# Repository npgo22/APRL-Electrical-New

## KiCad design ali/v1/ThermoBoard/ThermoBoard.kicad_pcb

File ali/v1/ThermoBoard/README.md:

# APRL Thermocouple Board
This is the "old" thermocouple board which was made
as an upgrade to old ALI.

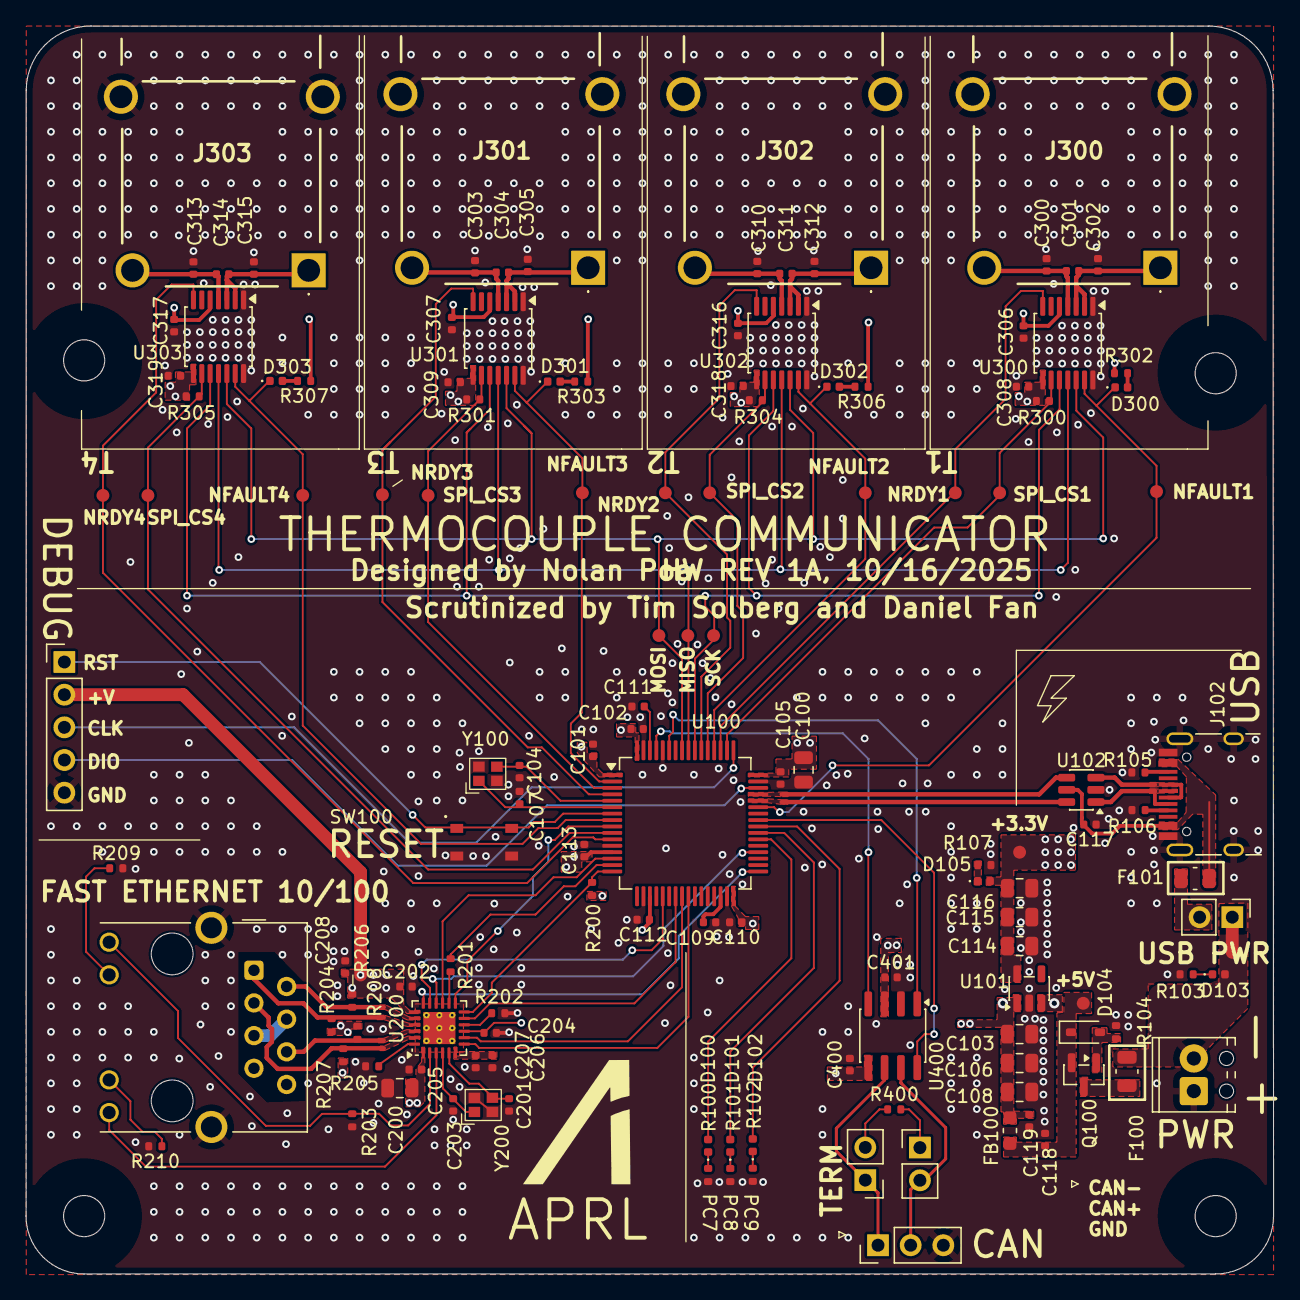
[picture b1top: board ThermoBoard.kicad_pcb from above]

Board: 4 copper layers, 97.0 x 97.0 mm, 138 parts (0 on the bottom side), 88 nets.

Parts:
C100, C103, C106, C108, C114, C115, C116, C200: 22u; C_0805_2012Metric
C101, C102, C105, C110, C112, C113, C117, C202, C204, C205, C301, C304, C306, C307, C308, C309, C311, C314, C316, C317, C318, C319, C400, C401: 100n; C_0402_1005Metric
C104, C107, C201, C203: 10p; C_0402_1005Metric
C109, C111: 2u2; C_0402_1005Metric
C118, C119, C206: 1u; C_0402_1005Metric
C207: 470p; C_0402_1005Metric
C208: 220n; C_0402_1005Metric
C300, C302, C303, C305, C310, C312, C313, C315: 10n; C_0402_1005Metric
D100, D101, D102, D103, D105, D300, D301, D302, D303: LED; LED_0402_1005Metric
D104: MM3Z10VT1G; SOD-323
F100: 300mA; Lute_16XR
F101: 500mA; Lute_16XR
FB100: FerriteBead; LSMGA160808T601RG
H1, H2, H3, H4: MountingHole; MountingHole_3.2mm_M3
J100: Conn_01x05_Pin; PinHeader_1x05_P2.54mm_Vertical
J101: Screw_Terminal_01x02; TerminalBlock_Phoenix_MPT-0,5-2-2.54_1x02_P2.54mm_Horizontal
J102: USB_C_Receptacle_USB2.0_16P; USB_C_Receptacle_HRO_TYPE-C-31-M-12
J200: RJ45_Hanrun_HR911105A_Horizontal
J300, J301, J302, J303: PCC-SMP-K-5; PCCSMPK5
J400: Conn_01x03; PinHeader_1x03_P2.54mm_Vertical
JP100, JP200, JP201: Jumper_2_Bridged; PinHeader_1x02_P2.54mm_Vertical
Q100: Si2371EDS; SOT-23
R100, R101, R102, R103, R104, R107, R202, R203, R209, R210, R300, R301, R302, R303, R304, R305, R306, R307: 10k; R_0402_1005Metric
R105, R106: 5.1k; R_0402_1005Metric
R200: 1.5k; R_0402_1005Metric
R201: 33R; R_0402_1005Metric
R204, R206, R207, R208: 47R; R_0402_1005Metric
R205: 12.1k; R_0402_1005Metric
R400: 120R; R_0402_1005Metric
SW100: SKRPANE010; SW-SMD_4P-L4.2-W3.2-P2.15-LS4.6-2
TP100, TP101, TP102, TP104, TP105, TP300, TP301, TP302, TP303, TP304, TP305, TP306, TP307, TP308, TP309, TP310, TP311: TestPoint_Small; TestPoint_Pad_D1.0mm
U100: STM32H563RITx; LQFP-64_10x10mm_P0.5mm
U101: AP2112K-3.3; SOT-23-5
U102: USBLC6-2SC6; SOT-23-6
U200: LAN8742A; VQFN-24-1EP_4x4mm_P0.5mm_EP2.5x2.5mm_ThermalVias
U300, U301, U302, U303: MAX31856; TSSOP-14_4.4x5mm_P0.65mm
U400: TJA1042T-3; SOIC-8_3.9x4.9mm_P1.27mm
Y100: 16MHz; CRYSTAL-SMD_4P-L2.0-W1.6-BL
Y200: 25MHz; CRYSTAL-SMD_4P-L2.0-W1.6-BL

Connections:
+3V3: C100.1, C101.1, C102.1, C105.1, C110.1, C112.1, C113.1, C114.2, C115.2, C116.2, C200.1, C202.1, C204.1, C205.1, C208.1, C306.1, C307.1, C308.1, C309.1, C316.1, C317.1, C318.1, C319.1, C400.1, D105.2 (A), J100.2, J200.4 (TCT), J200.5 (RCT), R200.1, R204.1, R206.1, R207.1, R208.1, R300.1, R301.1, R302.1, R303.1, R304.1, R305.1, R306.1, R307.1, TP104.1, U100.1 (VBAT), U100.13 (VDDA), U100.19 (VDD), U100.32 (VDD), U100.48 (VDD), U100.64 (VDD), U101.5 (VOUT), U200.1 (VDD2A), U200.9 (VDDIO), U200.19 (VDD1A), U300.5 (AVDD), U300.8 (DVDD), U301.5 (AVDD), U301.8 (DVDD), U302.5 (AVDD), U302.8 (DVDD), U303.5 (AVDD), U303.8 (DVDD), U400.5 (VIO)
+5V: C103.2, C106.2, C108.2, C119.1, C401.1, FB100.2, U101.1 (VIN), U101.3 (EN), U400.3 (VCC)
+VDC: D103.2 (A), F100.1, J101.2, JP100.1 (A)
/CAN/CAN+: J400.2, JP201.2 (B), U400.7 (CANH)
/CAN/CAN-: J400.1, JP200.1 (A), U400.6 (CANL)
/Ethernet/LED1-REGOFF: J200.12, U200.3 (LED1/REGOFF)
/Ethernet/LED2-INTSEL: J200.9, R203.1, U200.2 (LED2/~INTSEL)
/Ethernet/RX+: J200.3 (RD+), R207.2, U200.23 (RXP)
/Ethernet/RX-: J200.6 (RD-), R208.2, U200.22 (RXN)
/Ethernet/TX+: J200.1 (TD+), R204.2, U200.21 (TXP)
/Ethernet/TX-: J200.2 (TD-), R206.2, U200.20 (TXN)
/Microcontroller/NRST: J100.1, SW100.1, SW100.2, U100.7 (NRST)
/Microcontroller/SWCLK: J100.3, U100.49 (PA14(JTCK)
/Microcontroller/SWDIO: J100.4, U100.46 (PA13(JTMS)
/Microcontroller/USB_D+: U100.45 (PA12), U102.4 (I/O2)
/Microcontroller/USB_D-: U100.44 (PA11), U102.6 (I/O1)
/Thermocouples/T1+: C300.2, C301.1, J300.2 (+), U300.4 (T+)
/Thermocouples/T1-: C301.2, C302.1, J300.1 (K), U300.2 (BIAS), U300.3 (T-)
/Thermocouples/T2+: C310.2, C311.1, J302.2 (+), U302.4 (T+)
/Thermocouples/T2-: C311.2, C312.1, J302.1 (K), U302.2 (BIAS), U302.3 (T-)
/Thermocouples/T3+: C303.2, C304.1, J301.2 (+), U301.4 (T+)
/Thermocouples/T3-: C304.2, C305.1, J301.1 (K), U301.2 (BIAS), U301.3 (T-)
/Thermocouples/T4+: C313.2, C314.1, J303.2 (+), U303.4 (T+)
/Thermocouples/T4-: C314.2, C315.1, J303.1 (K), U303.2 (BIAS), U303.3 (T-)
ETH_CRS_DV: U100.23 (PA7), U200.11 (CRS_DV/MODE2)
ETH_MDC: U100.9 (PC1), U200.13 (MDC)
ETH_MDIO: R200.2, U100.16 (PA2), U200.12 (MDIO)
ETH_NRST: U100.14 (PA0), U200.15 (~RST)
ETH_REF_CLK: R201.1, U100.15 (PA1)
ETH_RXD0: U100.24 (PC4), U200.8 (RXD0/MODE0)
ETH_RXD1: U100.25 (PC5), U200.7 (RXD1/MODE1)
ETH_TXD0: U100.33 (PB12), U200.18 (TXD1)
ETH_TXD1: U100.36 (PB15), U200.16 (TXEN)
ETH_TX_EN: U100.21 (PA5), U200.17 (TXD0)
FDCAN_RX: U100.61 (PB8), U400.4 (RXD)
FDCAN_STDBY: U100.41 (PA8), U400.8 (STB)
FDCAN_TX: U100.59 (PB7), U400.1 (TXD)
GND: C100.2, C101.2, C102.2, C103.1, C104.2, C105.2, C106.1, C107.2, C108.1, C109.2, C110.2, C111.2, C112.2, C113.2, C114.1, C115.1, C116.1, C117.1, C118.2, C119.2, C200.2, C201.2, C202.2, C203.2, C204.2, C205.2, C206.2, C207.2, C208.2, C300.1, C302.2, C303.1, C305.2, C306.2, C307.2, C308.2, C309.2, C310.1, C312.2, C313.1, C315.2, C316.2, C317.2, C318.2, C319.2, C400.2, C401.2, J100.5, J101.1, J102.A1 (GND), J102.A12 (GND), J102.B1 (GND), J102.B12 (GND), J102.S1 (SHIELD), J200.8, J200.SH, J300.MH1, J300.MH2, J301.MH1, J301.MH2, J302.MH1, J302.MH2, J303.MH1, J303.MH2, J400.3, R100.1, R101.1, R102.1, R103.2, R104.1, R105.2, R106.2, R107.1, R202.1, R203.2, R205.2, R209.2, R210.2, SW100.3, SW100.4, U100.12 (VSSA), U100.18 (VSS), U100.31 (VSS), U100.47 (VSS), U100.60 (BOOT0), U100.63 (VSS), U101.2 (GND), U102.2 (GND), U200.25 (VSS), U300.1 (AGND), U300.14 (DGND), U301.1 (AGND), U301.14 (DGND), U302.1 (AGND), U302.14 (DGND), U303.1 (AGND), U303.14 (DGND), U400.2 (GND), Y100.2, Y100.4, Y200.2, Y200.4
NDRDY1: TP300.1, U100.51 (PC10), U300.7 (~DRDY)
NDRDY2: TP306.1, U100.54 (PD2), U302.7 (~DRDY)
NDRDY3: TP303.1, U100.4 (PC15), U301.7 (~DRDY)
NDRDY4: TP309.1, U100.11 (PC3), U303.7 (~DRDY)
NFAULT1: D300.1 (K), TP301.1, U100.43 (PA10), U300.13 (~FAULT)
NFAULT2: D302.1 (K), TP307.1, U100.52 (PC11), U302.13 (~FAULT)
NFAULT3: D301.1 (K), TP304.1, U100.2 (PC13), U301.13 (~FAULT)
NFAULT4: D303.1 (K), TP310.1, U100.8 (PC0), U303.13 (~FAULT)
unnamed: C109.1, U100.30 (VCAP)
unnamed: C111.1, U100.62 (VCAP)
unnamed: D100.2 (A), U100.38 (PC7)
unnamed: D100.1 (K), R100.2
unnamed: D101.2 (A), U100.39 (PC8)
unnamed: D101.1 (K), R101.2
unnamed: D102.2 (A), U100.40 (PC9)
unnamed: D102.1 (K), R102.2
unnamed: D103.1 (K), R103.1
unnamed: D104.2 (A), Q100.1 (G), R104.2
unnamed: C118.1, D104.1 (K), FB100.1, Q100.2 (S), TP105.1
unnamed: D105.1 (K), R107.2
unnamed: D300.2 (A), R302.2
unnamed: D301.2 (A), R303.2
unnamed: D302.2 (A), R306.2
unnamed: D303.2 (A), R307.2
unnamed: J102.A5 (CC1), R106.1
unnamed: J102.B5 (CC2), R105.1
unnamed: J102.A6 (D+), J102.B6 (D+), U102.3 (I/O2)
unnamed: J102.A7 (D-), J102.B7 (D-), U102.1 (I/O1)
unnamed: J200.10, R209.1
unnamed: J200.11, R210.1
unnamed: F101.1, JP100.2 (B)
unnamed: JP200.2 (B), R400.1
unnamed: JP201.1 (A), R400.2
unnamed: F100.2, Q100.3 (D)
unnamed: C104.1, U100.5 (PH0), Y100.3
unnamed: C107.1, U100.6 (PH1), Y100.1
unnamed: R205.1, U200.24 (RBIAS)
unnamed: R202.2, U200.10 (RXER/PHYAD0)
unnamed: C206.1, C207.1, U200.6 (VDDCR)
unnamed: C201.1, U200.5 (XTAL1/CLKIN), Y200.3
unnamed: C203.1, U200.4 (XTAL2), Y200.1
unnamed: R201.2, U200.14 (~INT/REFCLKO)
SPI_CS1: R300.2, TP302.1, U100.50 (PA15(JTDI)), U300.9 (~CS)
SPI_CS2: R304.2, TP308.1, U100.53 (PC12), U302.9 (~CS)
SPI_CS3: R301.2, TP305.1, U100.3 (PC14), U301.9 (~CS)
SPI_CS4: R305.2, TP311.1, U100.10 (PC2), U303.9 (~CS)
SPI_MISO: TP101.1, U100.56 (PB4(NJTRST)), U300.11 (SDO), U301.11 (SDO), U302.11 (SDO), U303.11 (SDO)
SPI_MOSI: TP102.1, U100.57 (PB5), U300.12 (SDI), U301.12 (SDI), U302.12 (SDI), U303.12 (SDI)
SPI_SCK: TP100.1, U100.55 (PB3(JTDO), U300.10 (SCK), U301.10 (SCK), U302.10 (SCK), U303.10 (SCK)
VBUS: C117.2, F101.2, J102.A4 (VBUS), J102.A9 (VBUS), J102.B4 (VBUS), J102.B9 (VBUS), U102.5 (VBUS)
